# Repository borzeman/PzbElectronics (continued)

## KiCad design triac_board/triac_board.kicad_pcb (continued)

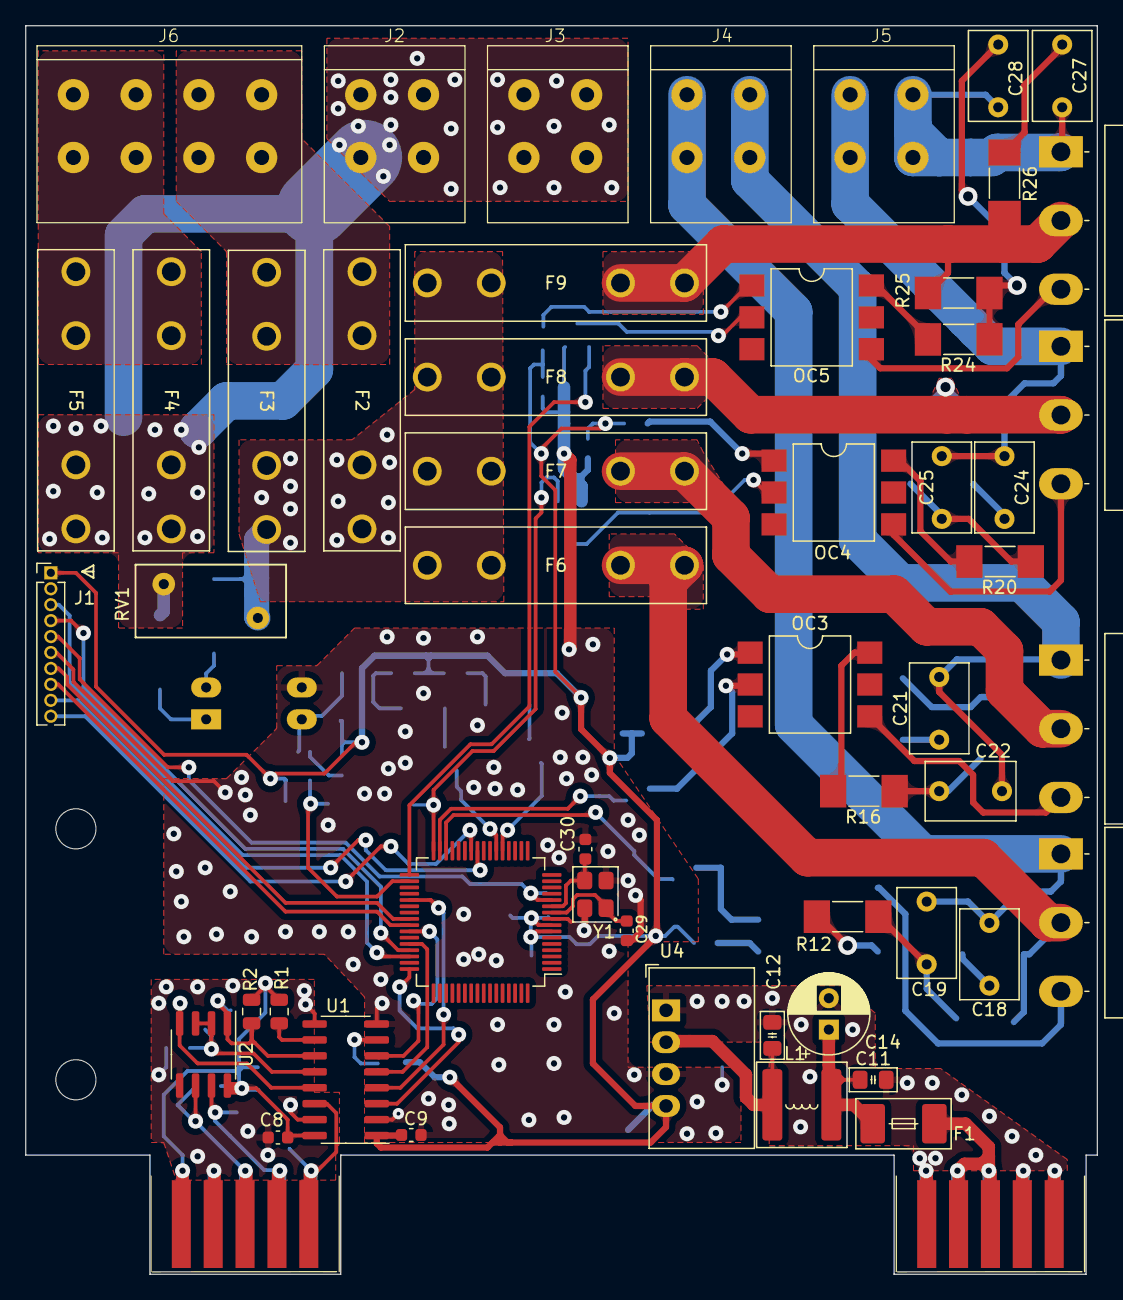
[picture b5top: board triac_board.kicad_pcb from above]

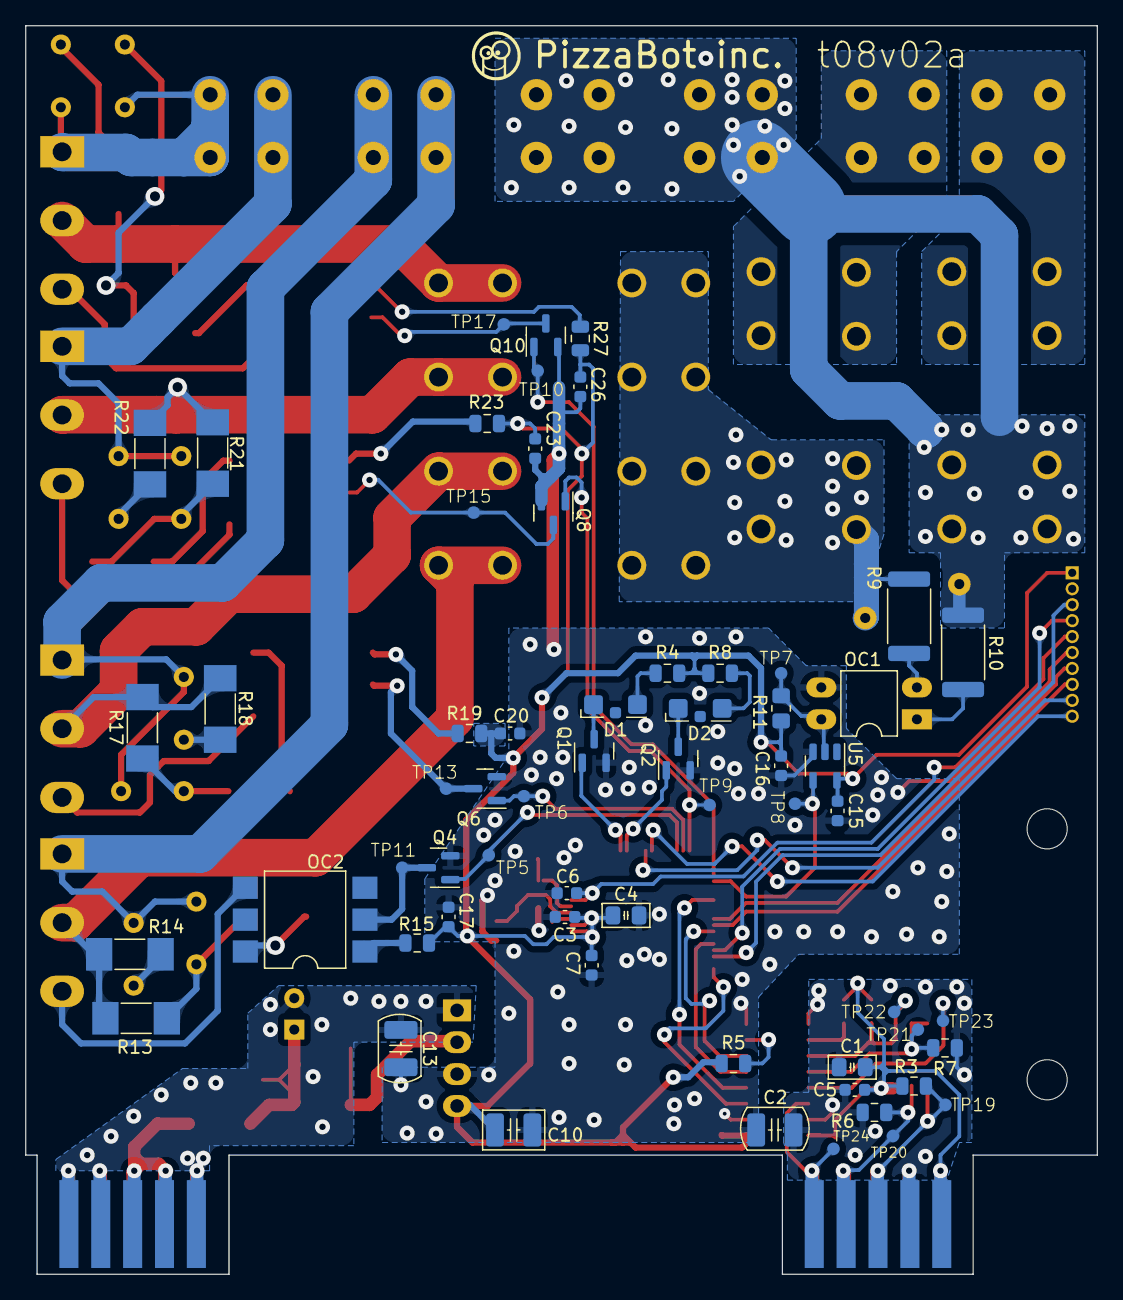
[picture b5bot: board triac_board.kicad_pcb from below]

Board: 2 copper layers, 85.4 x 99.5 mm, 117 parts (61 on the bottom side), 79 nets.

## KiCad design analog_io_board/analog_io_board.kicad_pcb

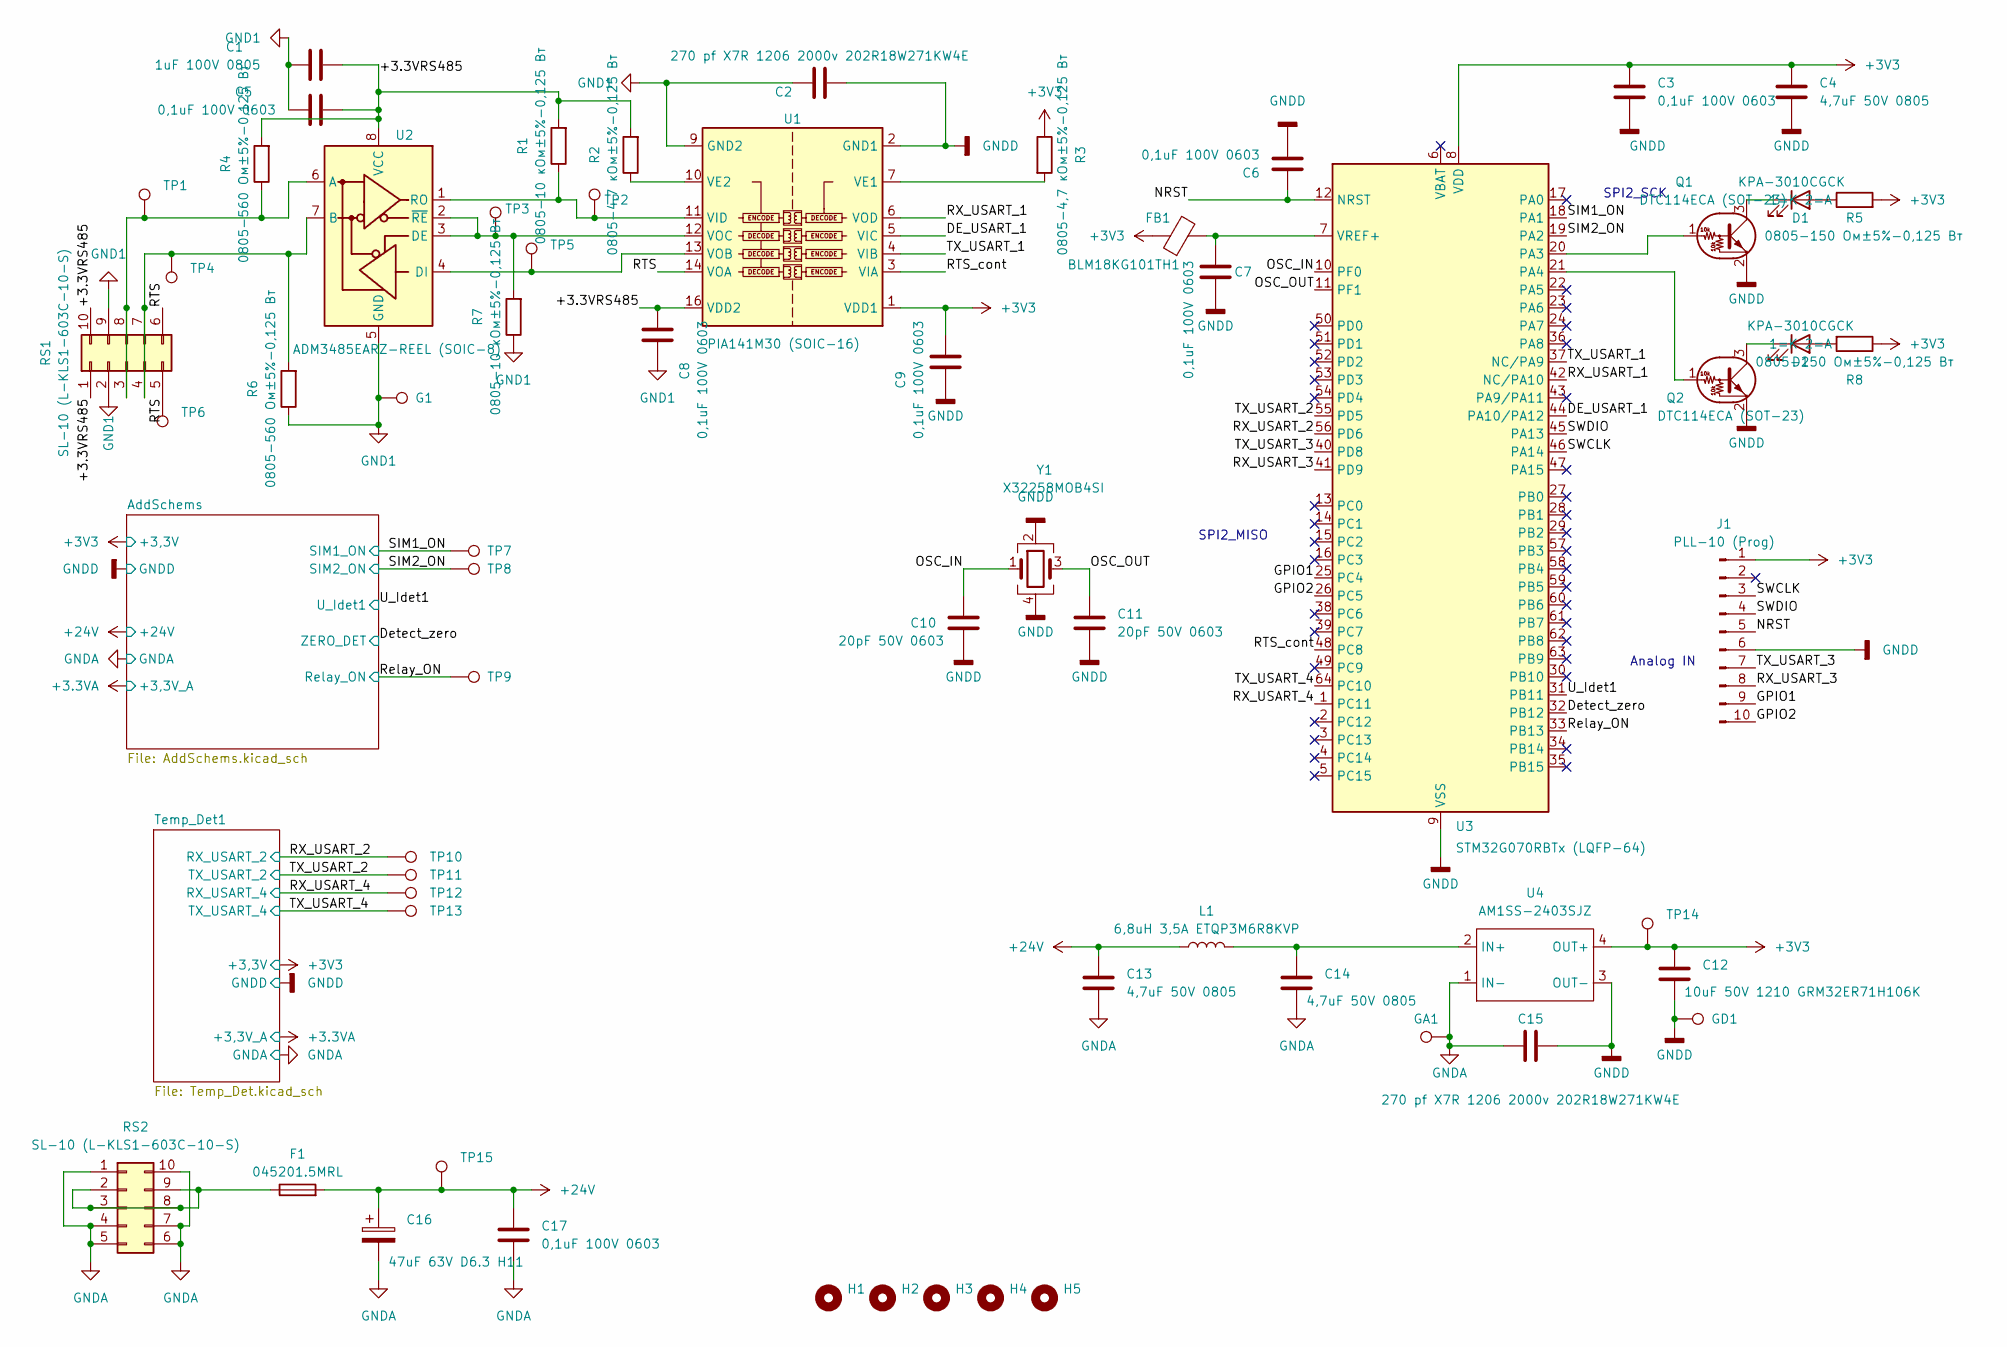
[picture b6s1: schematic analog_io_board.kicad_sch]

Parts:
C1: 1uF 100V 0805; C_0805_2012Metric
C2, C15: 270 pf X7R 1206 2000v 202R18W271KW4E; L_1210_3225Metric
C3, C5, C6, C7, C8, C9, C17: 0,1uF 100V 0603; C_0603_1608Metric
C4, C13, C14: 4,7uF 50V 0805; C_0805_2012Metric
C10, C11: 20pF 50V 0603; C_0603_1608Metric
C12: 10uF 50V 1210 GRM32ER71H106K; C_1210_3225Metric
C16: 47uF 63V D6.3 H11; C_Radial_D6.3mm_H11.0mm_P2.50mm
D1, D2: KPA-3010CGCK; LED_Kingbright_KPA-3010_3x2x1mm
F1: 045201.5MRL; Fuse_Littelfuse-NANO2-451_453
FB1: BLM18KG101TH1; L_0603_1608Metric
G1: TestPoint; TestPoint_Pad_D1.0mm
GA1: TestPoint; TestPoint_Pad_D1.0mm
GD1: TestPoint; TestPoint_Pad_D1.0mm
H1, H2, H3, H4, H5: MountingHole; MountingHole_3.2mm_M3
J1: PLL-10 (Prog); PinHeader_1x10_P1.27mm_Vertical
L1: 6,8uH 3,5A ETQP3M6R8KVP; L_Bourns-SRN6028
Q1, Q2: DTC114ECA (SOT-23); SOT-23
R1, R7: 0805-10 кОм±5%-0,125 Вт; R_0805_2012Metric
R2, R3: 0805-4,7 кОм±5%-0,125 Вт; R_0805_2012Metric
R4, R6: 0805-560 Ом±5%-0,125 Вт; R_0805_2012Metric
R5, R8: 0805-150 Ом±5%-0,125 Вт; R_0805_2012Metric
RS1, RS2: SL-10 (L-KLS1-603C-10-S); Edge_Conn_KLS1-603-10
TP1, TP2, TP3, TP4, TP5, TP6, TP7, TP8, TP9, TP10, TP11, TP12, TP13, TP14, TP15: TestPoint; TestPoint_Pad_D1.0mm
U1: PIA141M30 (SOIC-16); SOIC-16_3.9x9.9mm_P1.27mm
U2: ADM3485EARZ-REEL (SOIC-8); SOIC-8_3.9x4.9mm_P1.27mm
U3: STM32G070RBTx (LQFP-64); LQFP-64_10x10mm_P0.5mm
U4: AM1SS-2403SJZ; Converter_DCDC_Murata_MEE1SxxxxSC_THT
Y1: X32258MOB4SI; Crystal_SMD_3225-4Pin_3.2x2.5mm

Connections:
+3V3: C3.1, C4.1, C9.2, C12.1, FB1.1, J1.1, R3.1, R5.2, R8.1, TP14.1, U1.1 (VDD1), U3.8 (VDD), U4.4 (OUT+); also elsewhere on the board
+24V: C13.1, C16.1, C17.1, F1.2, L1.1, TP15.1; also elsewhere on the board
/+3.3VRS485: C1.2, C5.2, C8.2, R1.2, R2.2, R4.2, RS1.1, RS1.10, U1.16 (VDD2), U2.8 (VCC)
/DE_USART_1: U1.5 (VIC), U3.44 (PA10/PA12)
/Detect_zero: U3.32 (PB12); also elsewhere on the board
/GPIO1: J1.9, U3.25 (PC4)
/GPIO2: J1.10, U3.26 (PC5)
/NRST: C6.1, J1.5, U3.12 (NRST)
/OSC_IN: C10.1, U3.10 (PF0), Y1.1
/OSC_OUT: C11.1, U3.11 (PF1), Y1.3
/RTS: RS1.5, RS1.6, TP6.1, U1.14 (VOA)
/RTS_cont: U1.3 (VIA), U3.48 (PC8)
/RX_USART_1: U1.6 (VOD), U3.42 (NC/PA10)
/RX_USART_2: TP10.1, U3.56 (PD6); also elsewhere on the board
/RX_USART_3: J1.8, U3.41 (PD9)
/RX_USART_4: TP12.1, U3.1 (PC11); also elsewhere on the board
/Relay_ON: TP9.1, U3.33 (PB13); also elsewhere on the board
/SIM1_ON: TP7.1, U3.18 (PA1); also elsewhere on the board
/SIM2_ON: TP8.1, U3.19 (PA2); also elsewhere on the board
/SWCLK: J1.3, U3.46 (PA14)
/SWDIO: J1.4, U3.45 (PA13)
/TX_USART_1: U1.4 (VIB), U3.37 (NC/PA9)
/TX_USART_2: TP11.1, U3.55 (PD5); also elsewhere on the board
/TX_USART_3: J1.7, U3.40 (PD8)
/TX_USART_4: TP13.1, U3.64 (PC10); also elsewhere on the board
/U_Idet1: U3.31 (PB11); also elsewhere on the board
GND1: C1.1, C2.1, C5.1, C8.1, G1.1, R6.1, R7.1, RS1.2, RS1.9, U1.9 (GND2), U1.15 (GND2), U2.5 (GND)
GNDA: C13.2, C14.2, C15.1, C16.2, C17.2, GA1.1, RS2.1, RS2.4, RS2.5, RS2.6, RS2.7, RS2.10, U4.1 (IN-); also elsewhere on the board
GNDD: C2.2, C3.2, C4.2, C6.2, C7.2, C9.1, C10.2, C11.2, C12.2, C15.2, GD1.1, J1.6, Q1.2 (E), Q2.2 (E), U1.2 (GND1), U1.8 (GND1), U3.9 (VSS), U4.3 (OUT-), Y1.2, Y1.4; also elsewhere on the board
unnamed: D1.2 (A), R5.1
unnamed: D1.1 (K), Q1.3 (C)
unnamed: D2.2 (A), R8.2
unnamed: D2.1 (K), Q2.3 (C)
unnamed: Q1.1 (B), U3.20 (PA3)
unnamed: Q2.1 (B), U3.21 (PA4)
unnamed: R4.1, RS1.3, RS1.8, TP1.1, U2.6 (A)
unnamed: R6.2, RS1.4, RS1.7, TP4.1, U2.7 (B)
unnamed: F1.1, RS2.2, RS2.3, RS2.8, RS2.9
unnamed: R3.2, U1.7 (VE1)
unnamed: R2.1, U1.10 (VE2)
unnamed: R1.1, TP2.1, U1.11 (VID), U2.1 (RO)
unnamed: TP5.1, U1.13 (VOB), U2.4 (DI)
unnamed: R7.2, TP3.1, U1.12 (VOC), U2.2 (~RE), U2.3 (DE)
unnamed: C7.1, FB1.2, U3.7 (VREF+)
unnamed: C14.1, L1.2, U4.2 (IN+)

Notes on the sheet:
SPI2_SCK
SPI2_MISO
Analog IN

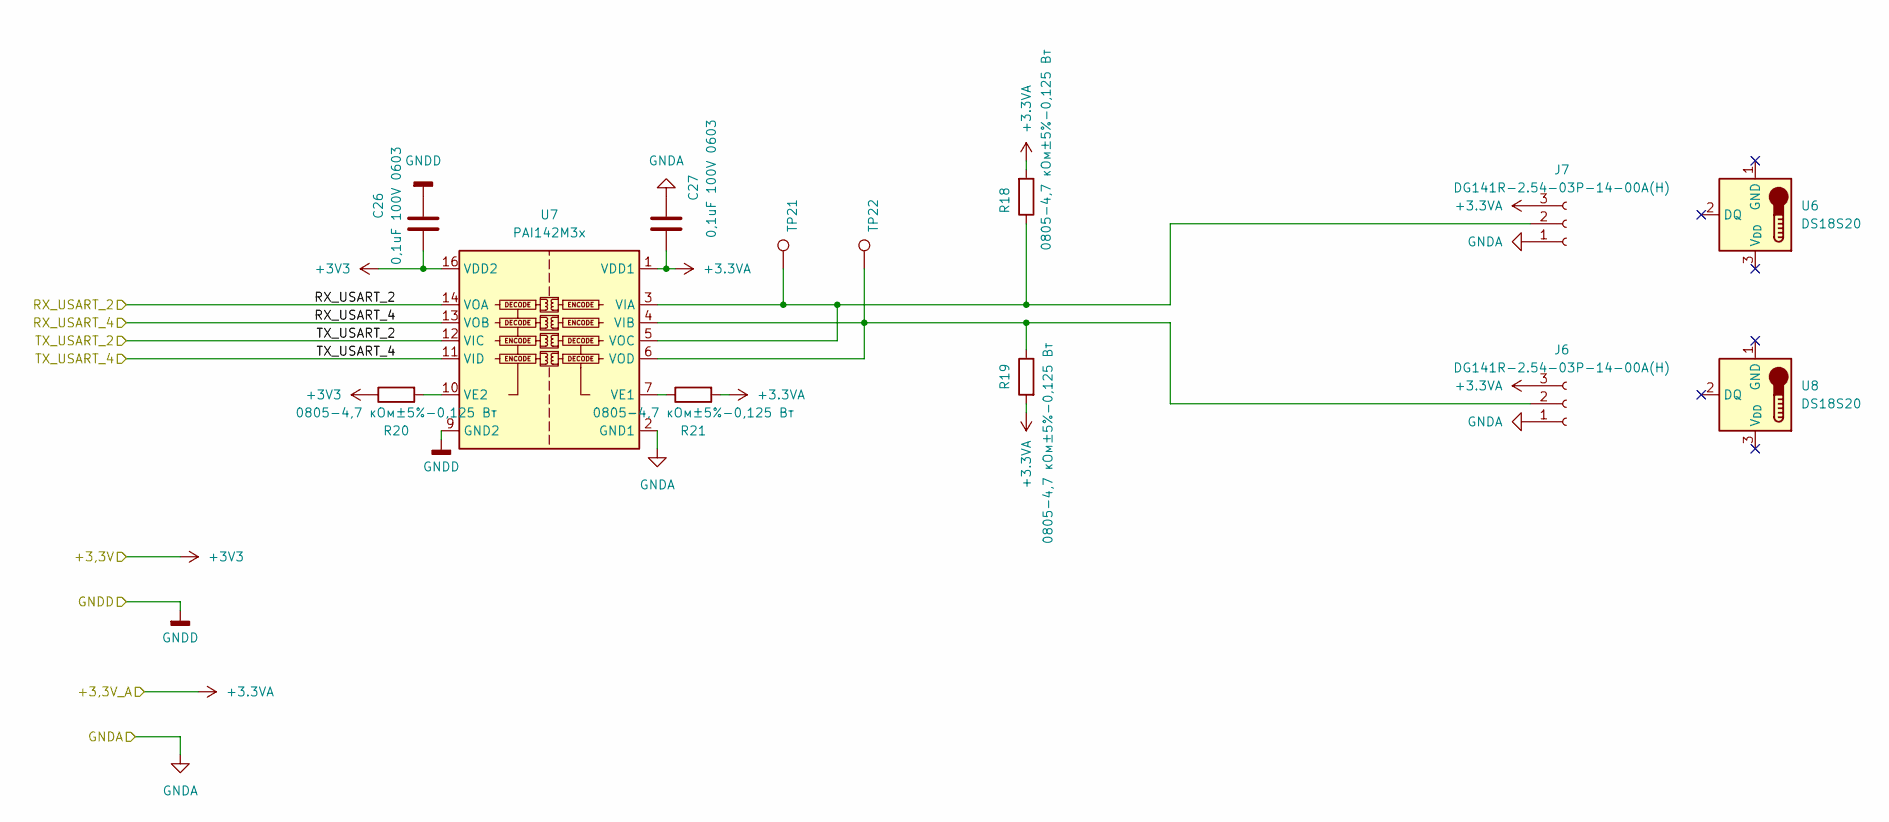
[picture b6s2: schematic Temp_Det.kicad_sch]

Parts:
C26, C27: 0,1uF 100V 0603; C_0603_1608Metric
J6, J7: DG141R-2.54-03P-14-00A(H); DG141R-2.54-03P
R18, R19, R20, R21: 0805-4,7 кОм±5%-0,125 Вт; R_0805_2012Metric
TP21, TP22: TestPoint; TestPoint_Pad_D1.0mm
U6, U8: DS18S20; TO-92_Inline
U7: PAI142M3x; SOIC-16_3.9x9.9mm_P1.27mm

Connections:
+3.3VA: C27.2, J6.3, J7.3, R18.2, R19.2, R21.2, U7.1 (VDD1); also elsewhere on the board
+3V3: C26.2, R20.1, U7.16 (VDD2); also elsewhere on the board
/RX_USART_2: U7.14 (VOA); also elsewhere on the board
/RX_USART_4: U7.13 (VOB); also elsewhere on the board
/TX_USART_2: U7.12 (VIC); also elsewhere on the board
/TX_USART_4: U7.11 (VID); also elsewhere on the board
GNDA: C27.1, J6.1, J7.1, U7.2 (GND1), U7.8 (GND1); also elsewhere on the board
GNDD: C26.1, U7.9 (GND2), U7.15 (GND2); also elsewhere on the board
unnamed: J6.2, R19.1, TP22.1, U7.4 (VIB), U7.6 (VOD)
unnamed: J7.2, R18.1, TP21.1, U7.3 (VIA), U7.5 (VOC)
unnamed: R21.1, U7.7 (VE1)
unnamed: R20.2, U7.10 (VE2)

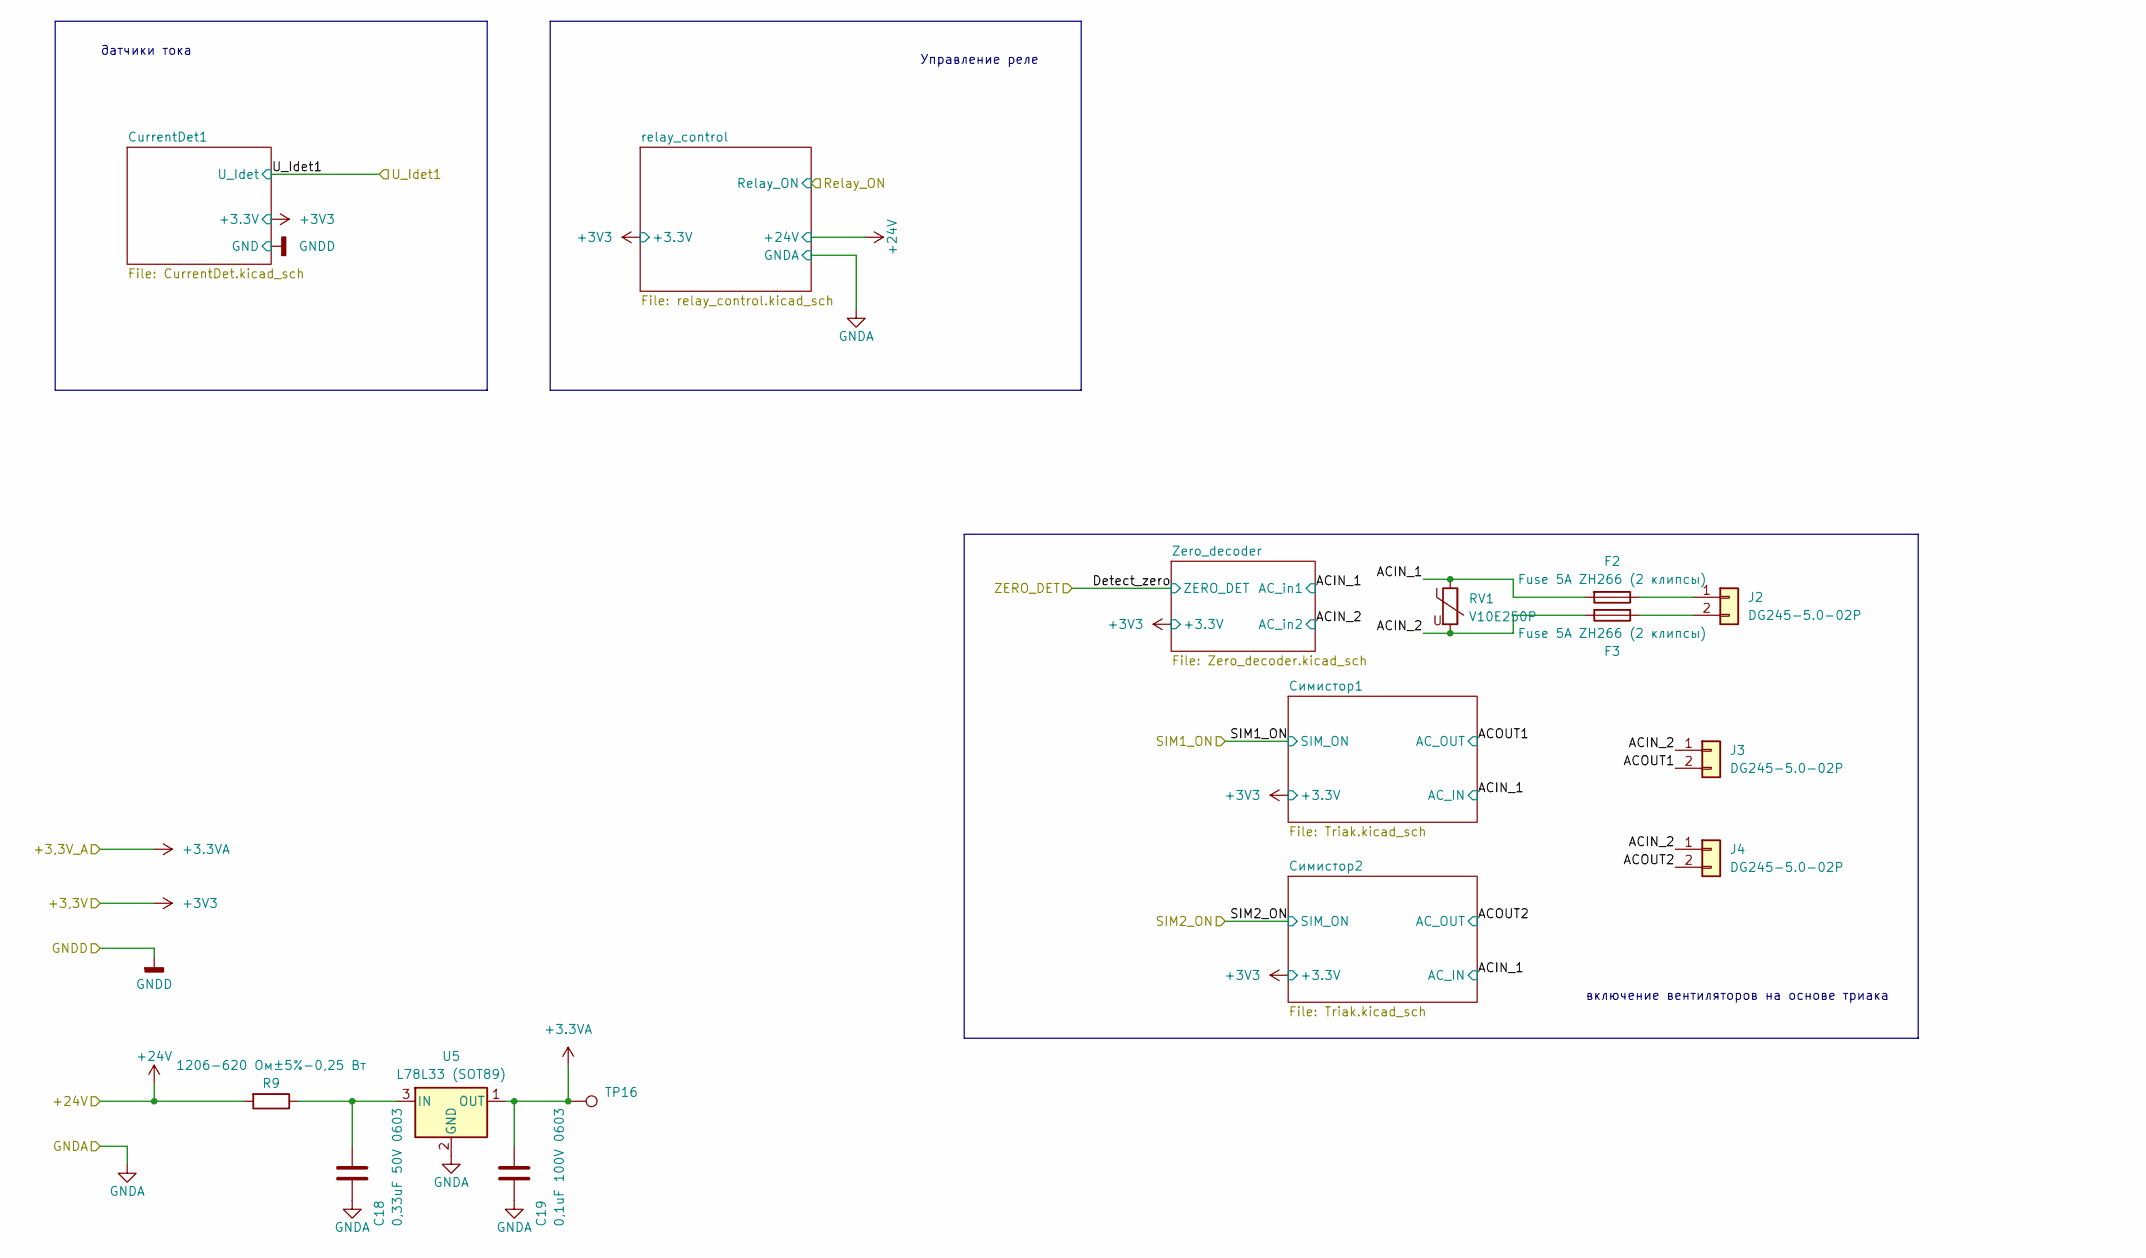
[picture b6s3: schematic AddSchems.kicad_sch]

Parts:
C18: 0,33uF 50V 0603; C_0603_1608Metric
C19: 0,1uF 100V 0603; C_0603_1608Metric
F2, F3: Fuse 5A ZH266 (2 клипсы); Fuseholder_100_series_5x20mm_D1,5
J2, J3, J4: DG245-5.0-02P
R9: 1206-620 Ом±5%-0,25 Вт; R_1206_3216Metric
RV1: V10E250P; RV_Disc_D12mm_W5.8mm_P7.5mm
TP16: TestPoint; TestPoint_Pad_D1.0mm
U5: L78L33 (SOT89); SOT-89-3

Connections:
+3.3VA: C19.1, TP16.1, U5.1 (OUT); also elsewhere on the board
+24V: R9.2; also elsewhere on the board
/AddSchems/ACIN_1: F2.2, RV1.1; also elsewhere on the board
/AddSchems/ACIN_2: F3.1, J3.1, J4.1, RV1.2; also elsewhere on the board
/AddSchems/ACOUT1: J3.2; also elsewhere on the board
/AddSchems/ACOUT2: J4.2; also elsewhere on the board
GNDA: C18.2, C19.2, U5.2 (GND); also elsewhere on the board
unnamed: F2.1, J2.1
unnamed: F3.2, J2.2
unnamed: C18.1, R9.1, U5.3 (IN)

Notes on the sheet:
Управление реле
включение вентиляторов на основе триака
датчики тока

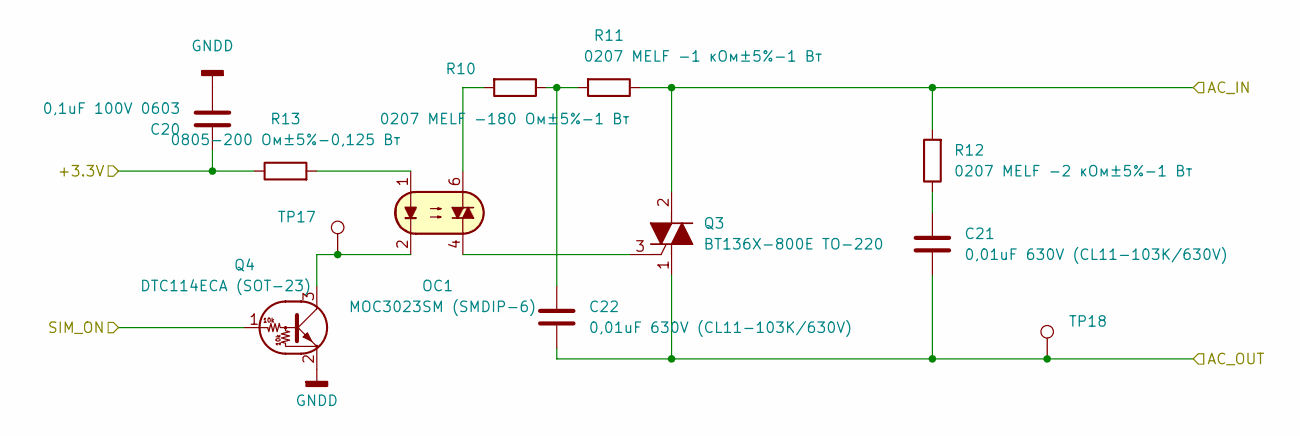
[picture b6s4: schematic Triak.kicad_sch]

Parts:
C20: 0,1uF 100V 0603; C_0603_1608Metric
C21, C22: 0,01uF 630V (CL11-103K/630V); C_Rect_L7.0mm_W4.5mm_P5.00mm
OC1: MOC3023SM (SMDIP-6); SMDIP-6_W9.53mm
Q3: BT136X-800E TO-220; TO-220-3_Horizontal_TabDown
Q4: DTC114ECA (SOT-23); SOT-23
R10: 0207 MELF -180 Ом±5%-1 Вт; R_MELF_MMB-0207
R11: 0207 MELF -1 кОм±5%-1 Вт; R_MELF_MMB-0207
R12: 0207 MELF -2 кОм±5%-1 Вт; R_MELF_MMB-0207
R13: 0805-200 Ом±5%-0,125 Вт; R_0805_2012Metric
TP17, TP18: TestPoint; TestPoint_Pad_D1.0mm

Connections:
+3V3: C20.1, R13.1; also elsewhere on the board
/AddSchems/ACIN_1: Q3.2 (A2), R11.1, R12.2; also elsewhere on the board
/AddSchems/ACOUT1: C21.2, C22.2, Q3.1 (A1), TP18.1; also elsewhere on the board
/SIM1_ON: Q4.1 (B); also elsewhere on the board
GNDD: C20.2, Q4.2 (E); also elsewhere on the board
unnamed: C21.1, R12.1
unnamed: C22.1, R10.1, R11.2
unnamed: OC1.1, R13.2
unnamed: OC1.6, R10.2
unnamed: OC1.4, Q3.3 (G)
unnamed: OC1.2, Q4.3 (C), TP17.1

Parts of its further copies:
C23: 0,1uF 100V 0603; C_0603_1608Metric
C24, C39: 0,01uF 630V (CL11-103K/630V); C_Rect_L7.0mm_W4.5mm_P5.00mm
OC2: MOC3023SM (SMDIP-6); SMDIP-6_W9.53mm
Q5: BT136X-800E TO-220; TO-220-3_Horizontal_TabDown
Q6: DTC114ECA (SOT-23); SOT-23
R17: 0805-200 Ом±5%-0,125 Вт; R_0805_2012Metric
R38: 0207 MELF -2 кОм±5%-1 Вт; R_MELF_MMB-0207
R39: 0207 MELF -180 Ом±5%-1 Вт; R_MELF_MMB-0207
R40: 0207 MELF -1 кОм±5%-1 Вт; R_MELF_MMB-0207
TP19, TP20: TestPoint; TestPoint_Pad_D1.0mm

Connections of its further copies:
+3V3: C23.1, R17.1; also elsewhere on the board
/AddSchems/ACIN_1: Q5.2 (A2), R38.2, R40.1; also elsewhere on the board
/AddSchems/ACOUT2: C24.2, C39.2, Q5.1 (A1), TP20.1; also elsewhere on the board
/SIM2_ON: Q6.1 (B); also elsewhere on the board
GNDD: C23.2, Q6.2 (E); also elsewhere on the board
unnamed: C24.1, R39.1, R40.2
unnamed: C39.1, R38.1
unnamed: OC2.1, R17.2
unnamed: OC2.6, R39.2
unnamed: OC2.4, Q5.3 (G)
unnamed: OC2.2, Q6.3 (C), TP19.1

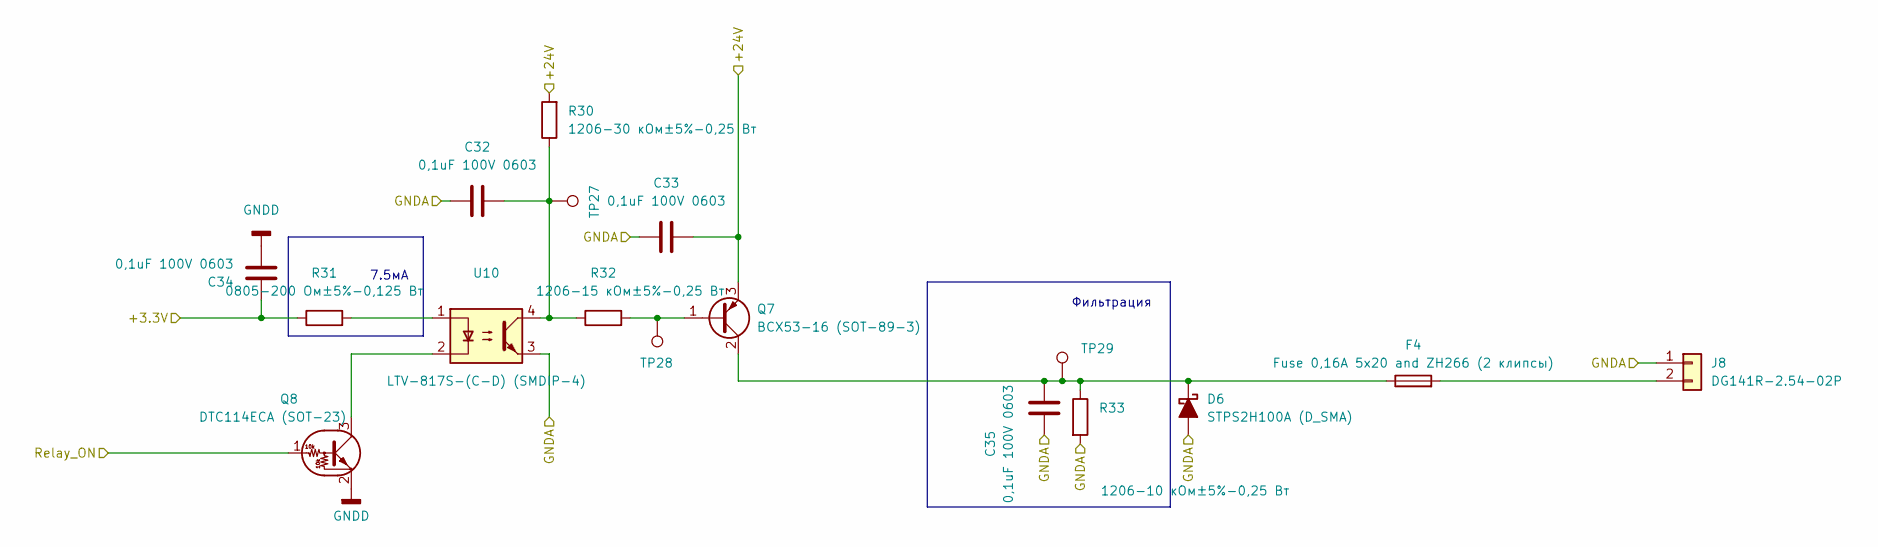
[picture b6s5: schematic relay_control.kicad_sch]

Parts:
C32, C33, C34, C35: 0,1uF 100V 0603; C_0603_1608Metric
D6: STPS2H100A (D_SMA); D_SMA
F4: Fuse 0,16A 5x20 and ZH266 (2 клипсы); Fuseholder_100_series_5x20mm_D1,5
J8: DG141R-2.54-02P; DG141R-02
Q7: BCX53-16 (SOT-89-3); SOT-89-3
Q8: DTC114ECA (SOT-23); SOT-23
R30: 1206-30 кОм±5%-0,25 Вт; R_1206_3216Metric
R31: 0805-200 Ом±5%-0,125 Вт; R_0805_2012Metric
R32: 1206-15 кОм±5%-0,25 Вт; R_1206_3216Metric
R33: 1206-10 кОм±5%-0,25 Вт; R_1206_3216Metric
TP27, TP28, TP29: TestPoint; TestPoint_Pad_D1.0mm
U10: LTV-817S-(С-D) (SMDIP-4); SMDIP-4_W9.53mm

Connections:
+3V3: C34.1, R31.1; also elsewhere on the board
+24V: C33.1, Q7.3 (E), R30.2; also elsewhere on the board
/Relay_ON: Q8.1 (B); also elsewhere on the board
GNDA: C32.2, C33.2, C35.2, D6.2 (A), J8.1, R33.2, U10.3; also elsewhere on the board
GNDD: C34.2, Q8.2 (E); also elsewhere on the board
unnamed: C32.1, R30.1, R32.1, TP27.1, U10.4
unnamed: C35.1, D6.1 (K), F4.1, Q7.2 (C), R33.1, TP29.1
unnamed: F4.2, J8.2
unnamed: Q7.1 (B), R32.2, TP28.1
unnamed: Q8.3 (C), U10.2
unnamed: R31.2, U10.1

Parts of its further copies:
C23: 0,1uF 100V 0603; C_0603_1608Metric
Q6: DTC114ECA (SOT-23); SOT-23

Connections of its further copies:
+3V3: C23.1; also elsewhere on the board
/SIM2_ON: Q6.1 (B); also elsewhere on the board
GNDD: C23.2, Q6.2 (E); also elsewhere on the board
unnamed 64: Q6.3 (C); also elsewhere on the board

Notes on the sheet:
7.5мА
Фильтрация

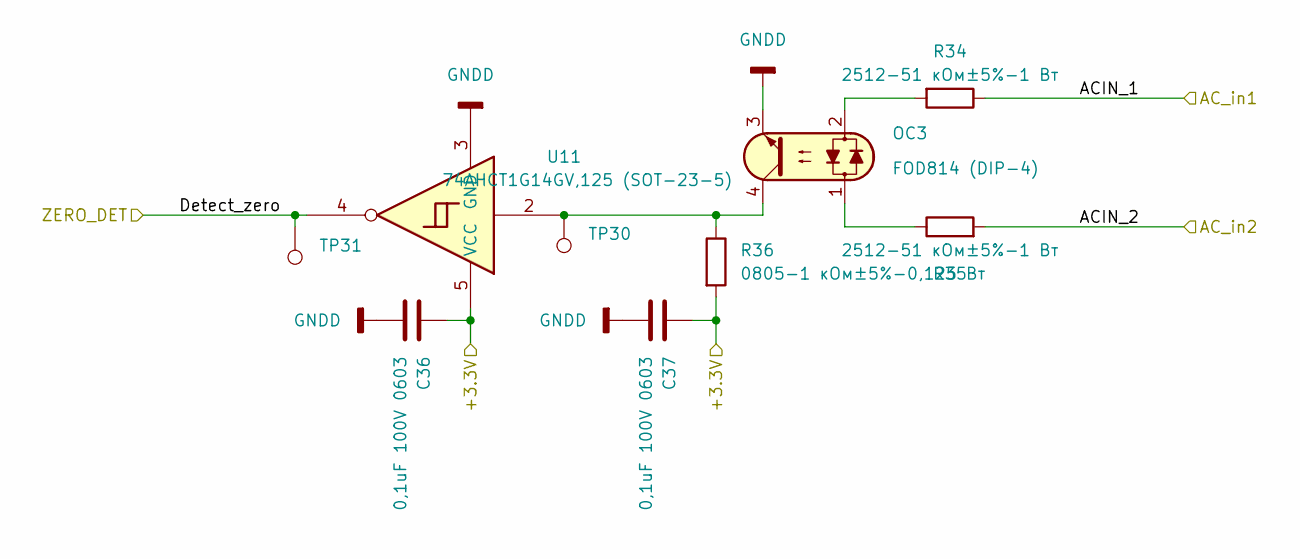
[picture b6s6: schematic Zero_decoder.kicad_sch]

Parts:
C36, C37: 0,1uF 100V 0603; C_0603_1608Metric
OC3: FOD814 (DIP-4); DIP-4_W7.62mm_LongPads
R34, R35: 2512-51 кОм±5%-1 Вт; R_2512_6332Metric
R36: 0805-1 кОм±5%-0,125 Вт; R_0805_2012Metric_Pad1.20x1.40mm_HandSolder
TP30, TP31: TestPoint; TestPoint_Pad_D1.0mm
U11: 74AHCT1G14GV,125 (SOT-23-5); SOT-23-5

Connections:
+3V3: C36.1, C37.1, R36.2, U11.5 (VCC); also elsewhere on the board
/AddSchems/ACIN_1: R34.1; also elsewhere on the board
/AddSchems/ACIN_2: R35.2; also elsewhere on the board
/Detect_zero: TP31.1, U11.4; also elsewhere on the board
GNDD: C36.2, C37.2, OC3.3, U11.3 (GND); also elsewhere on the board
unnamed: OC3.1, R35.1
unnamed: OC3.2, R34.2
unnamed: OC3.4, R36.1, TP30.1, U11.2

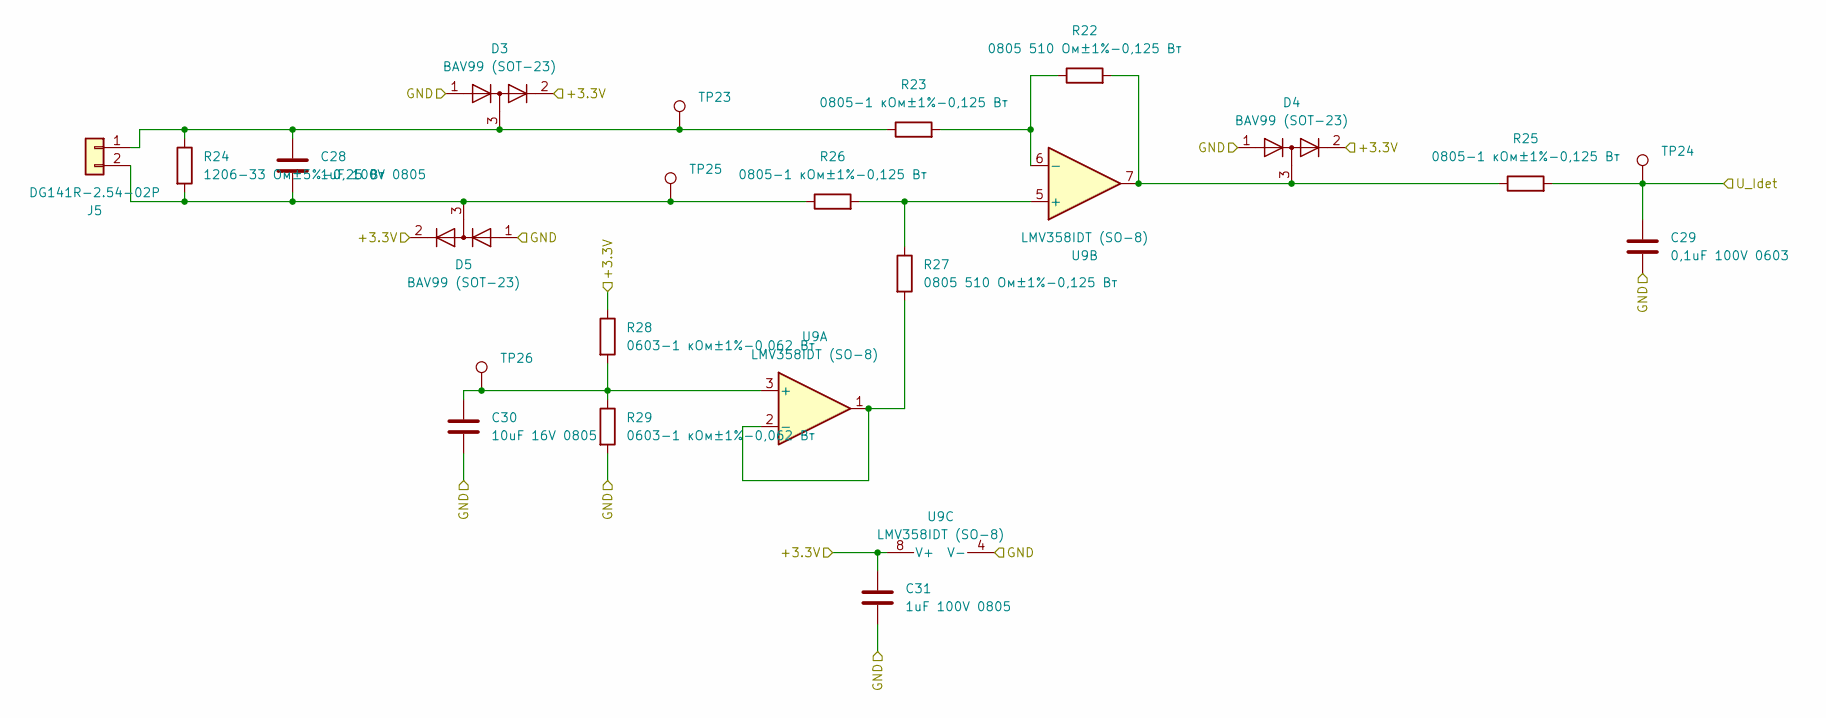
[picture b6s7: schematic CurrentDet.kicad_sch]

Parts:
C28, C31: 1uF 100V 0805; C_0805_2012Metric
C29: 0,1uF 100V 0603; C_0603_1608Metric
C30: 10uF 16V 0805; C_0805_2012Metric
D3, D4, D5: BAV99 (SOT-23); SOT-23
J5: DG141R-2.54-02P; DG141R-02
R22, R27: 0805 510 Ом±1%-0,125 Вт; R_0805_2012Metric
R23, R25, R26: 0805-1 кОм±1%-0,125 Вт; R_0805_2012Metric
R24: 1206-33 Ом±5%-0,25 Вт; R_1206_3216Metric_Pad1.30x1.75mm_HandSolder
R28, R29: 0603-1 кОм±1%-0,062 Вт; R_0603_1608Metric
TP23, TP24, TP25, TP26: TestPoint; TestPoint_Pad_D1.0mm
U9: LMV358IDT (SO-8); SO-8_3.9x4.9mm_P1.27mm

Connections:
+3V3: C31.1, D3.2 (A), D4.2 (A), D5.2 (A), R28.1, U9.8 (V+); also elsewhere on the board
/U_Idet1: C29.1, R25.2, TP24.1; also elsewhere on the board
GNDD: C29.2, C30.2, C31.2, D3.1 (K), D4.1 (K), D5.1 (K), R29.2, U9.4 (V-); also elsewhere on the board
unnamed: D4.3 (K), R22.2, R25.1, U9.7
unnamed: C28.1, D3.3 (K), J5.1, R23.1, R24.1, TP23.1
unnamed: C28.2, D5.3 (K), J5.2, R24.2, R26.1, TP25.1
unnamed: C30.1, R28.2, R29.1, TP26.1, U9.3 (+)
unnamed: R27.2, U9.1, U9.2 (-)
unnamed: R26.2, R27.1, U9.5 (+)
unnamed: R22.1, R23.2, U9.6 (-)
